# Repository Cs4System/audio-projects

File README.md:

# audio-projects
## XLR-RCA Interface

- Small stereo XLR-RCA interface
- Based on IN137 and DRV134 
- Power supply +-15V 
- With LDO-Regulator to +-12V

Front:

Back:

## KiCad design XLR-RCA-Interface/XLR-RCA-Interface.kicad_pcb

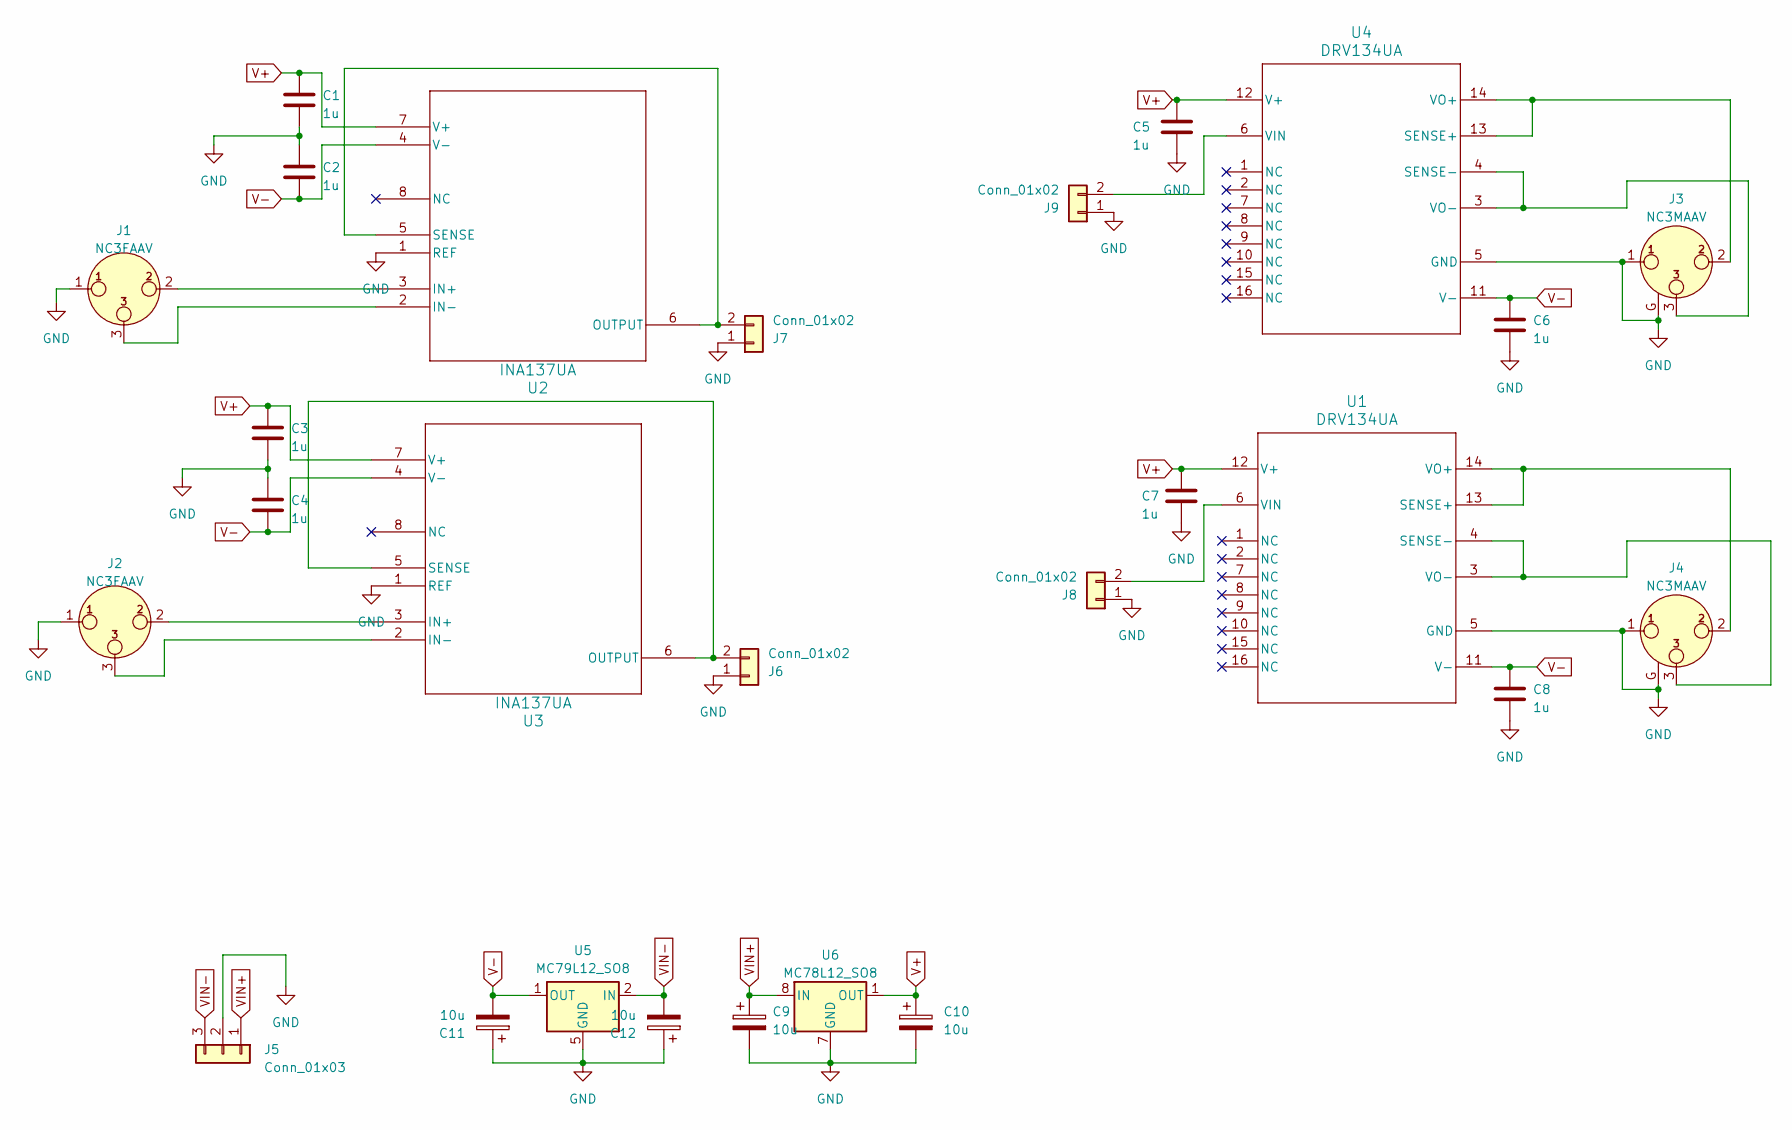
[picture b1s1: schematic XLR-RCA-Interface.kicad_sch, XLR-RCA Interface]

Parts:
C1, C2, C3, C4, C5, C6, C7, C8: 1u; C_0603_1608Metric_Pad1.08x0.95mm_HandSolder
C9, C10, C11, C12: 10u; CP_Elec_4x4.5
J1, J2: NC3FAAV; Jack_XLR_Neutrik_NC3FAAV_Vertical
J3, J4: NC3MAAV; Jack_XLR_Neutrik_NC3MAAV_Vertical
J5: Conn_01x03; PinHeader_1x03_P2.54mm_Vertical
J6, J7, J8, J9: Conn_01x02; PinHeader_1x02_P2.54mm_Vertical
U1, U4: DRV134UA; SOIC-16W_7.5x10.3mm_P1.27mm
U2, U3: INA137UA; SOIC-8_3.9x4.9mm_P1.27mm
U5: MC79L12_SO8; SOIC-8_3.9x4.9mm_P1.27mm
U6: MC78L12_SO8; SOIC-8_3.9x4.9mm_P1.27mm

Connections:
GND: C1.2, C2.1, C3.2, C4.1, C5.2, C6.2, C7.2, C8.2, C9.2, C10.2, C11.1, C12.1, J1.1, J2.1, J3.1, J3.G, J4.1, J4.G, J5.2, J6.1, J7.1, J8.1, J9.1, U1.5 (GND), U2.1 (REF), U3.1 (REF), U4.5 (GND), U5.5 (GND), U6.2 (GND), U6.3 (GND), U6.6 (GND), U6.7 (GND)
unnamed: J6.2, U3.5 (SENSE), U3.6 (OUTPUT)
unnamed: J7.2, U2.5 (SENSE), U2.6 (OUTPUT)
unnamed: J8.2, U1.6 (VIN)
unnamed: J9.2, U4.6 (VIN)
unnamed: J4.2, U1.13 (SENSE+), U1.14 (VO+)
unnamed: J4.3, U1.3 (VO-), U1.4 (SENSE-)
unnamed: J1.2, U2.3 (IN+)
unnamed: J1.3, U2.2 (IN-)
unnamed: J2.2, U3.3 (IN+)
unnamed: J2.3, U3.2 (IN-)
unnamed: J3.2, U4.13 (SENSE+), U4.14 (VO+)
unnamed: J3.3, U4.3 (VO-), U4.4 (SENSE-)
V+: C1.1, C3.1, C5.1, C7.1, C10.1, U1.12 (V+), U2.7 (V+), U3.7 (V+), U4.12 (V+), U6.1 (OUT)
V-: C2.2, C4.2, C6.1, C8.1, C11.2, U1.11 (V-), U2.4 (V-), U3.4 (V-), U4.11 (V-), U5.1 (OUT)
VIN+: C9.1, J5.1, U6.8 (IN)
VIN-: C12.2, J5.3, U5.2 (IN), U5.3 (IN), U5.6 (IN), U5.7 (IN)

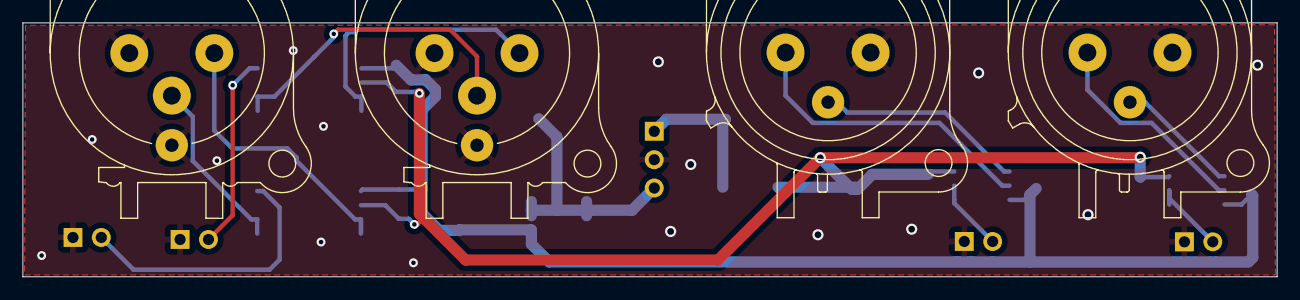
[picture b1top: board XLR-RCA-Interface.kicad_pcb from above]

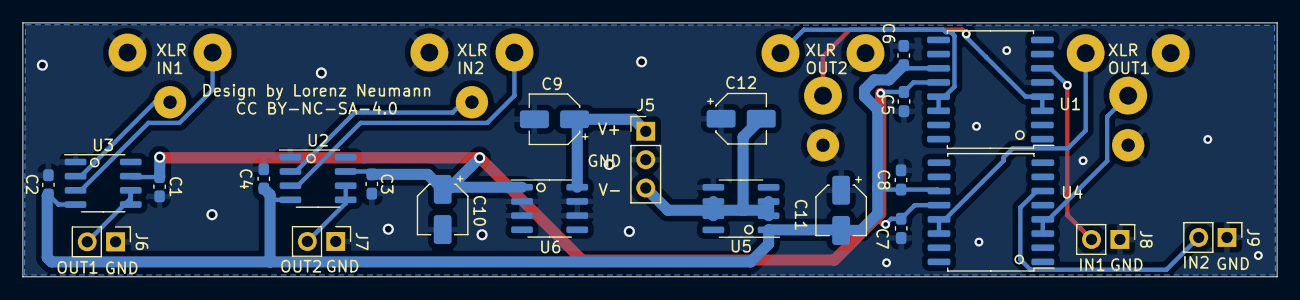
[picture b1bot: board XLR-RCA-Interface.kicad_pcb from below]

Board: 2 copper layers, 112.4 x 22.8 mm, 27 parts (23 on the bottom side), 17 nets.

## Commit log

2023-11-09 Added stereo XLR-RCA interface design
2023-11-09 Added README,BOM and picture

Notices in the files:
XLR-RCA-Interface/XLR-RCA-Interface.kicad_pcb:
CC BY-NC-SA-4.0
